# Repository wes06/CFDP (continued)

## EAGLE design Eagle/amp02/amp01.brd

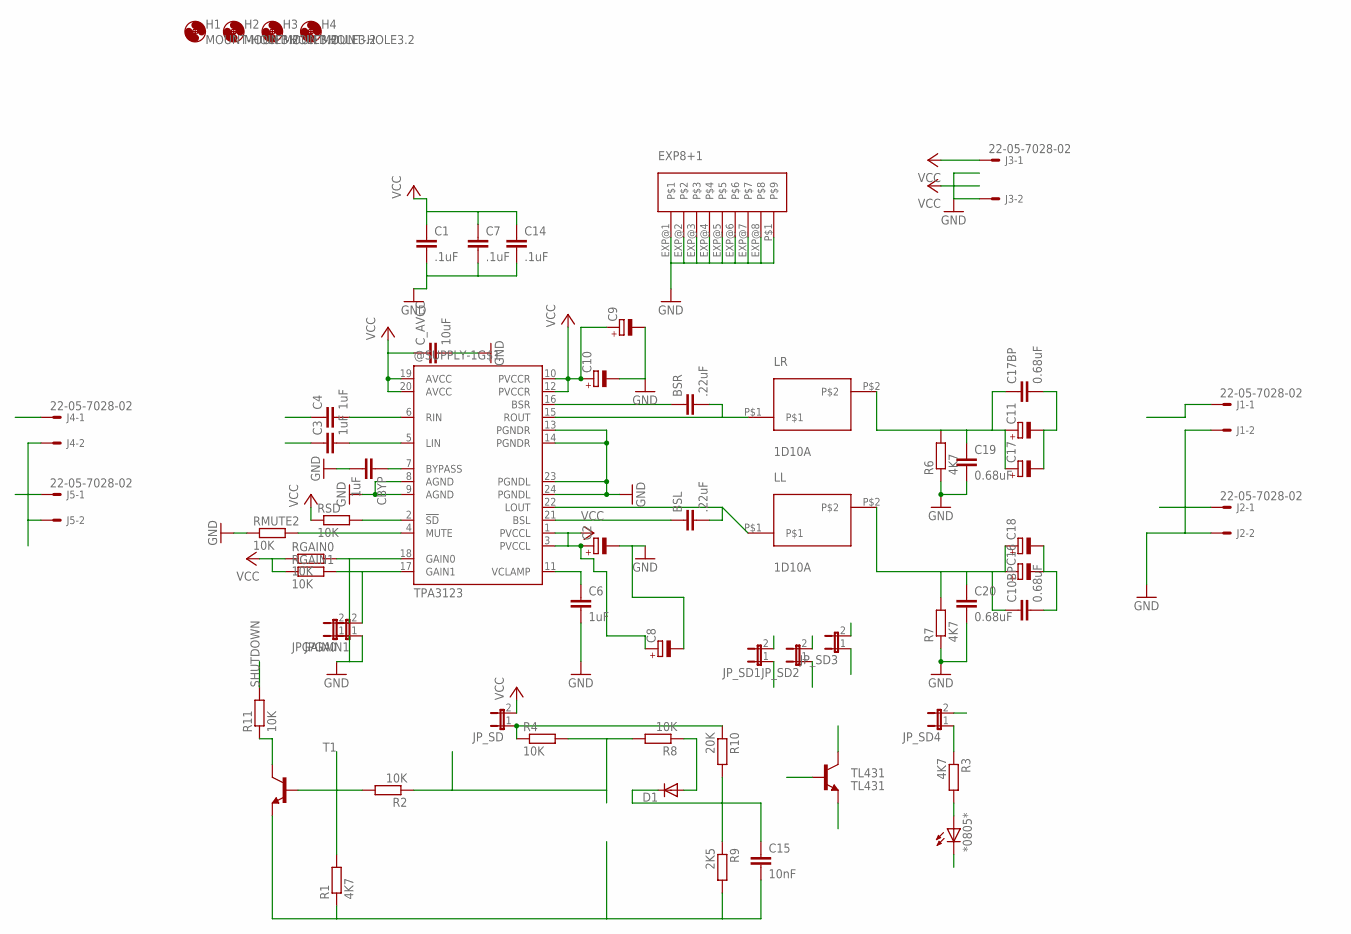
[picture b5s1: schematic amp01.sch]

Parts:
*0805*: LEDCHIP-LED0805; CHIP-LED0805
@SUPPLY-1: TPA3123; PWP-TSSOP24
BSL: .22uF; C0805
BSR: .22uF; C0805
C1, C7, C14: .1uF; C0805
C2, C8, C9, C10, C11, C16, C17, C18: CPOL-EUF; PANASONIC_F
C3, C4: 1uF; C050-050X075
C6: 1uF; C0805
C10BP, C17BP, C19, C20: 0.68uF; C050-055X075
C15: 10nF; C0805
CBYP: 1uF; C0805
C_AVCC: 10uF; C1210
D1: DIODE-MICROMELF-W; MICROMELF-W
H1, H2, H3, H4: MOUNT-HOLE3.2; 3,2
J1, J2, J3, J4, J5: 22-05-7028-02; 7395-02
JPGAIN0, JPGAIN1: JUMPER-2SMD-NC; SJ_2S
JP_SD, JP_SD1, JP_SD2, JP_SD3, JP_SD4: JUMPER-2SMD-NC; SJ_2S
LL: 1D10A; 1D10APAC
LR: 1D10A; 1D10APAC
R1, R3, R6, R7: 4K7; R0805
R2, R4, R8, R11: 10K; R0805
R9: 2K5; R0805
R10: 20K; R0805
RGAIN0, RGAIN1: 10K; R0805
RMUTE2: 10K; R0805
RSD: 10K; R0805
T1: MMBT3904LT1-NPN-SOT23-BEC; SOT23-BEC
TL431: TL431; SOT23

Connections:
GND: *0805*.C, @SUPPLY-1.8 (AGND), @SUPPLY-1.9 (AGND), @SUPPLY-1.13 (PGNDR), @SUPPLY-1.14 (PGNDR), @SUPPLY-1.23 (PGNDL), @SUPPLY-1.24 (PGNDL), @SUPPLY-1.EXP@1, @SUPPLY-1.EXP@2, @SUPPLY-1.EXP@3, @SUPPLY-1.EXP@4, @SUPPLY-1.EXP@5, @SUPPLY-1.EXP@6, @SUPPLY-1.EXP@7, @SUPPLY-1.EXP@8, @SUPPLY-1.P$1, C1.2, C2.-, C6.2, C7.2, C8.-, C9.-, C10.-, C14.2, C15.2, C19.2, C20.2, CBYP.2, C_AVCC.2, J1.2, J2.2, J3.2, J4.2, J5.2, JPGAIN0.1, JPGAIN1.1, JP_SD1.1, JP_SD2.1, JP_SD3.1, R1.1, R6.1, R7.1, R9.2, RMUTE2.1, T1.E, TL431.3 (C)
GND1: JP_SD1.2
GND2: JP_SD2.2, JP_SD3.2
K: R2.1, R4.2, R8.2, TL431.1 (B)
LOUT: C11.-, C17.-, C17BP.2, J1.1
unnamed: @SUPPLY-1.6 (RIN), C4.2
unnamed: @SUPPLY-1.5 (LIN), C3.2
unnamed: C3.1, J5.1
unnamed: JP_SD.1, R4.1, R10.1
unnamed: @SUPPLY-1.11 (VCLAMP), C6.1
unnamed: @SUPPLY-1.4 (MUTE), RMUTE2.2
unnamed: @SUPPLY-1.18 (GAIN0), JPGAIN0.2, RGAIN0.2
unnamed: @SUPPLY-1.17 (GAIN1), JPGAIN1.2, RGAIN1.2
unnamed: C4.1, J4.1
unnamed: @SUPPLY-1.15 (ROUT), BSR.2, LR.P$1
unnamed: @SUPPLY-1.16 (BSR), BSR.1
unnamed: @SUPPLY-1.22 (LOUT), BSL.2, LL.P$1
unnamed: @SUPPLY-1.21 (BSL), BSL.1
unnamed: C10BP.1, C16.+, C18.+, C20.1, LL.P$2, R7.2
unnamed: R1.2, R2.2, T1.B
unnamed: *0805*.A, R3.2
unnamed: C11.+, C17.+, C17BP.1, C19.1, LR.P$2, R6.2
unnamed: JP_SD4.1, R3.1
unnamed: R11.1, T1.C
unnamed: D1.A, R8.1
REF: C15.1, D1.C, R9.1, R10.2, TL431.2 (E)
ROUT: C10BP.2, C16.-, C18.-, J2.1
SHUTDOWN: @SUPPLY-1.2 (!SD), R11.2, RSD.2
VBYP: @SUPPLY-1.7 (BYPASS), CBYP.1
VCC: @SUPPLY-1.1 (PVCCL), @SUPPLY-1.3 (PVCCL), @SUPPLY-1.10 (PVCCR), @SUPPLY-1.12 (PVCCR), @SUPPLY-1.19 (AVCC), @SUPPLY-1.20 (AVCC), C1.1, C2.+, C7.1, C8.+, C9.+, C10.+, C14.1, C_AVCC.1, J3.1, JP_SD.2, JP_SD4.2, RGAIN0.1, RGAIN1.1, RSD.1

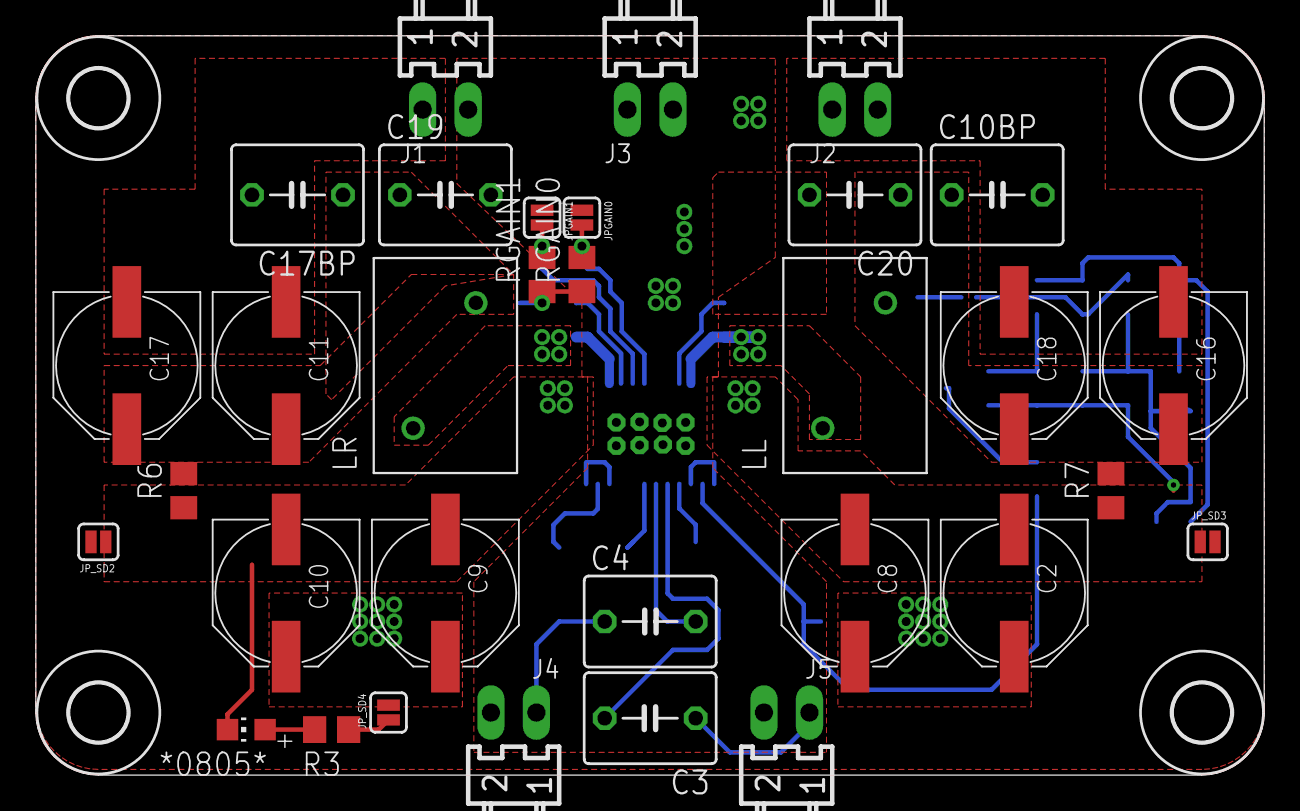
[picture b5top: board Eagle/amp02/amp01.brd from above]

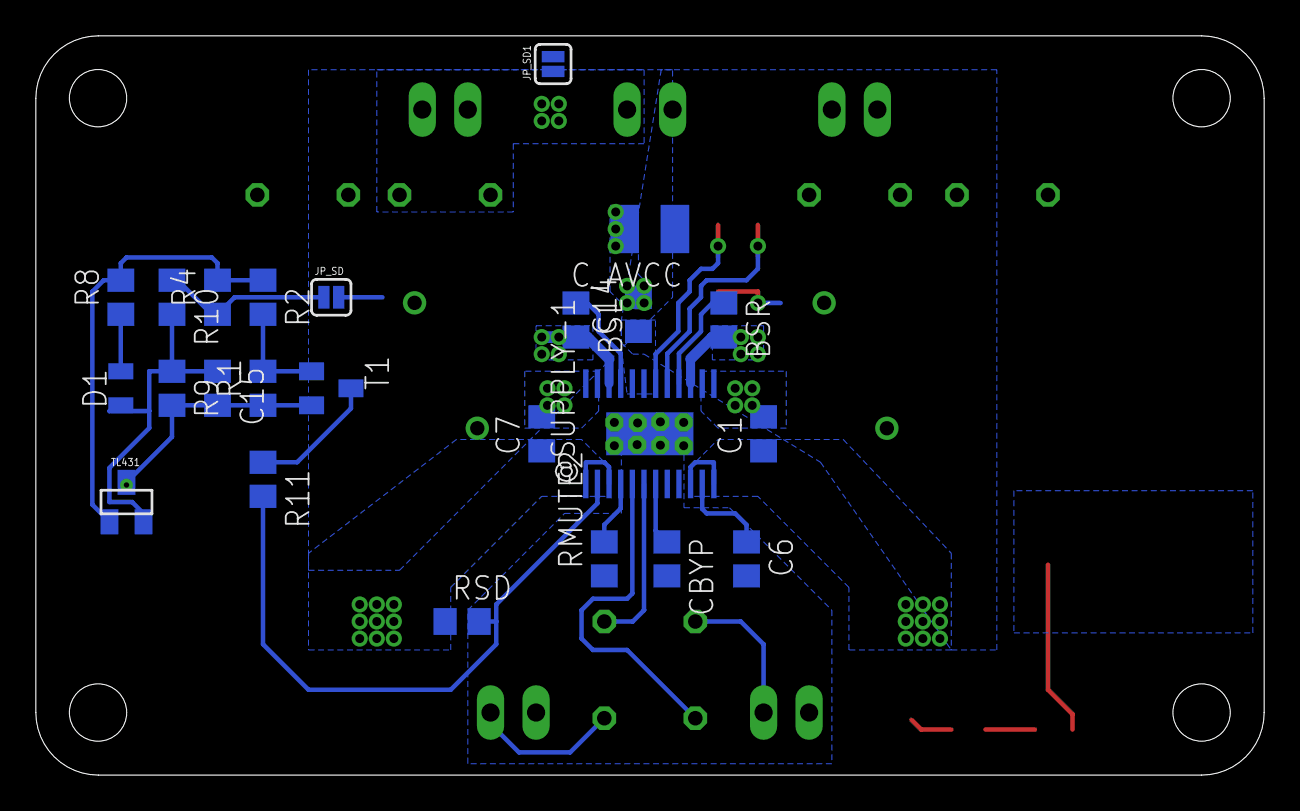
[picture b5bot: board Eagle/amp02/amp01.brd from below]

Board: 2 copper layers, 68.6 x 41.3 mm, 60 parts (24 on the bottom side), 29 nets.

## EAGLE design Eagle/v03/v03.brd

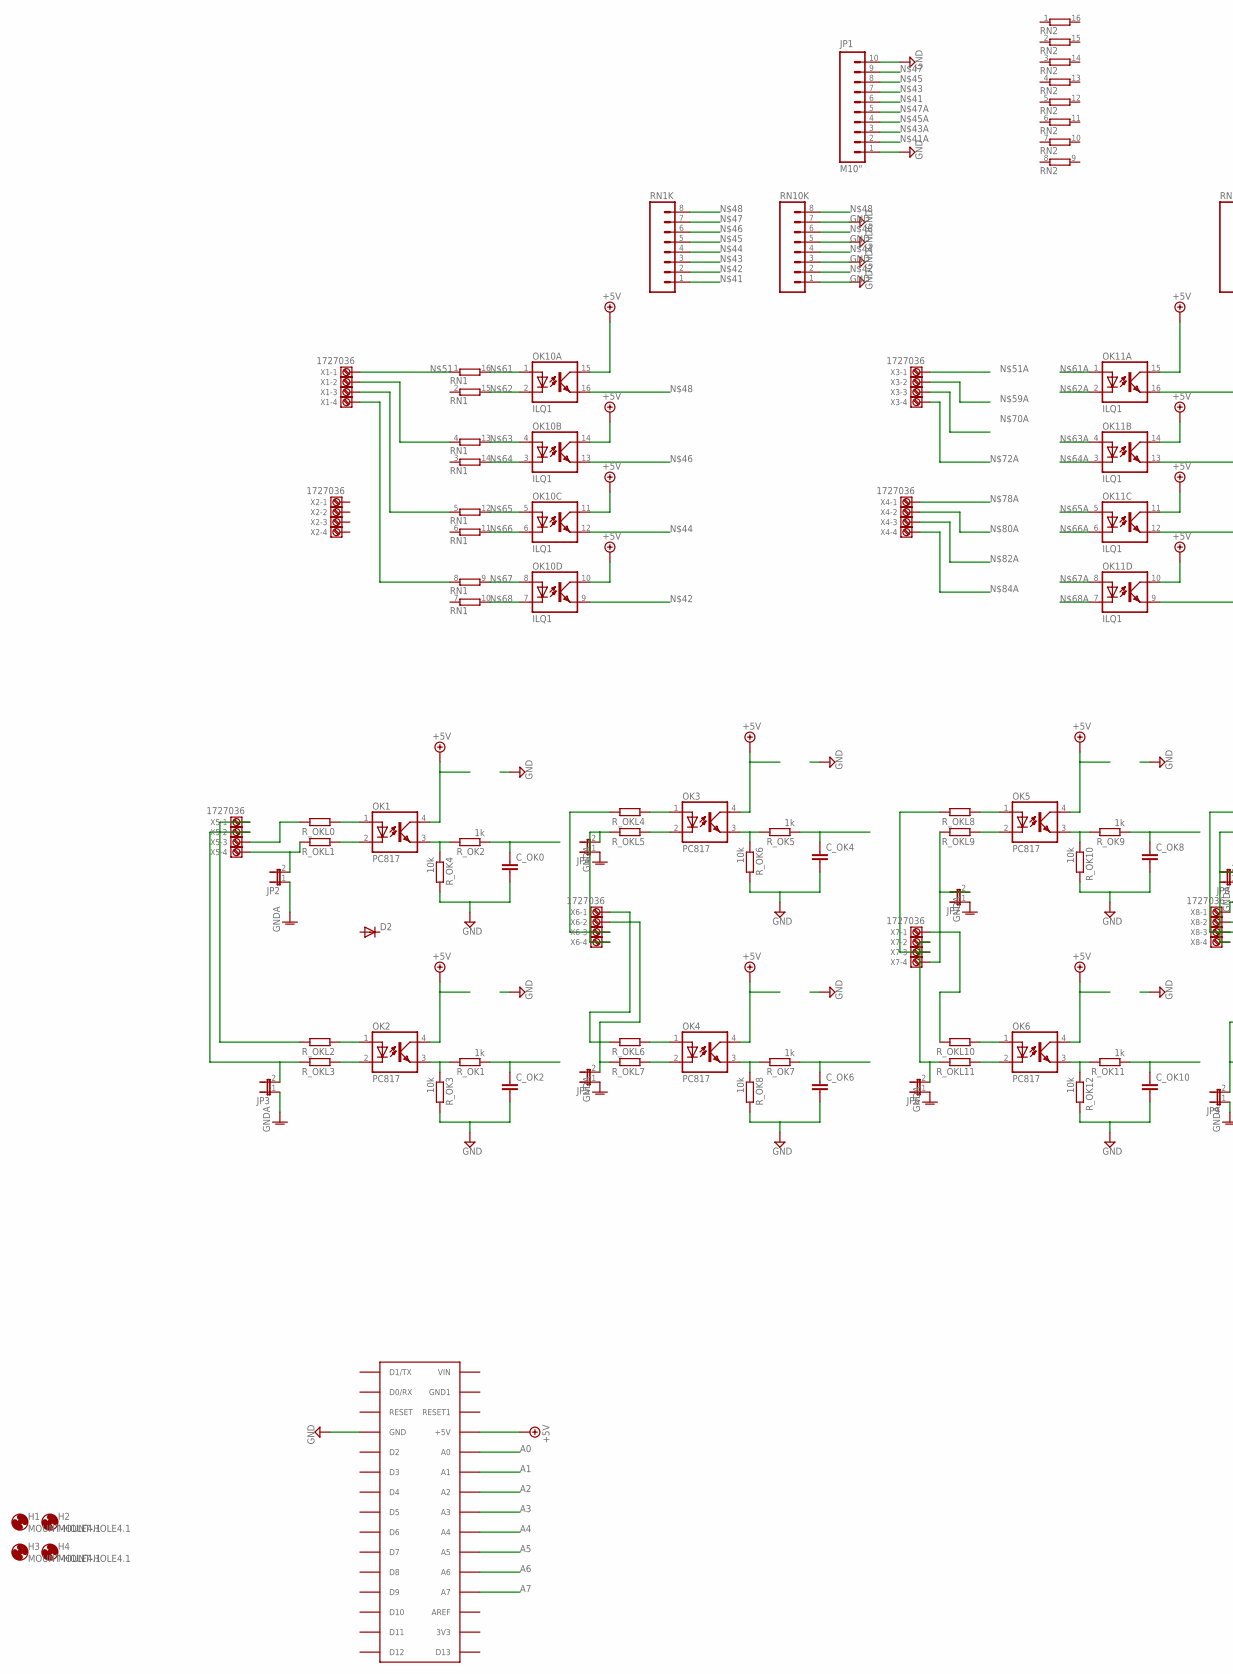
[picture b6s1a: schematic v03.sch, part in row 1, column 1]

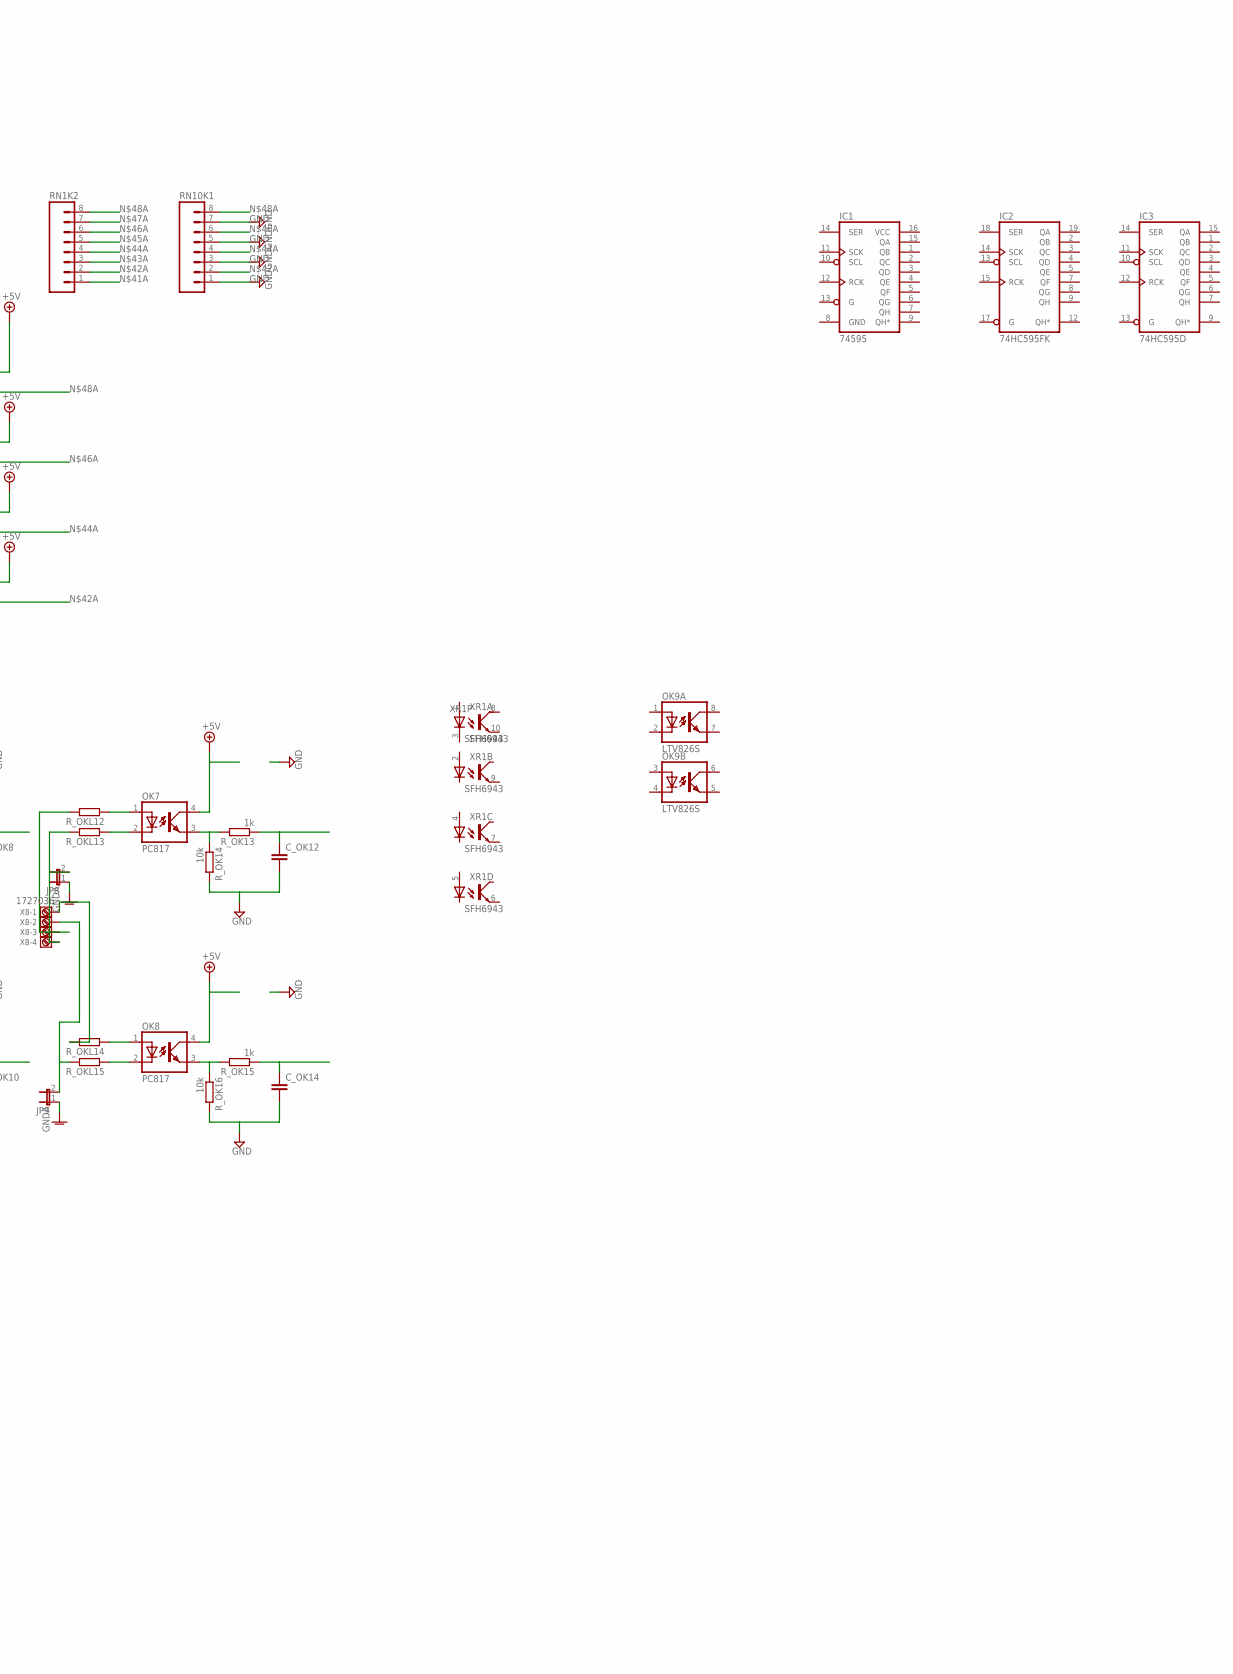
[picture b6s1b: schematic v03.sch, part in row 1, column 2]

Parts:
C_OK0, C_OK2, C_OK4, C_OK6, C_OK8, C_OK10, C_OK12, C_OK14: C-EUC0805; C0805
D2: DIODESOD; SOD-323
H1, H2, H3, H4: MOUNT-HOLE4.1; 4,1
IC1: 74595; TSSOP16
IC2: 74HC595FK; LCC20
IC3: 74HC595D; SO16
JP1: M10"; 1X10
JP2, JP3, JP4, JP5, JP6, JP7, JP8, JP9: JUMPER-2PTH; 1X02
OK1, OK2, OK3, OK4, OK5, OK6, OK7, OK8: PC817; DIL04
OK9: LTV826S; DIL8-SMD
OK10, OK11: ILQ1; DIL16
RN1, RN2: 8R-PSOMC; SOMC16
RN1K, RN1K2, RN10K, RN10K1: M081X08; 1X08
R_OK1, R_OK2, R_OK5, R_OK7, R_OK9, R_OK11, R_OK13, R_OK15: 1k; M0805
R_OK3, R_OK4, R_OK6, R_OK8, R_OK10, R_OK12, R_OK14, R_OK16: 10k; M0805
R_OKL0, R_OKL1, R_OKL2, R_OKL3, R_OKL4, R_OKL5, R_OKL6, R_OKL7, R_OKL8, R_OKL9, R_OKL10, R_OKL11, R_OKL12, R_OKL13, R_OKL14, R_OKL15: R-EU_R1210; R1210
U$1: ARDUINONANO; PDIP-32
X1, X2, X3, X4, X5, X6, X7, X8: 1727036
XR1: SFH6943; SOT223/10

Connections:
+5V: OK1.4 (COL), OK2.4 (COL), OK3.4 (COL), OK4.4 (COL), OK5.4 (COL), OK6.4 (COL), OK7.4 (COL), OK8.4 (COL), OK10.10 (COL), OK10.11 (COL), OK10.14 (COL), OK10.15 (COL), OK11.10 (COL), OK11.11 (COL), OK11.14 (COL), OK11.15 (COL), U$1.+5V
A0: C_OK0.1, R_OK2.1, U$1.A0
A1: C_OK2.1, R_OK1.1, U$1.A1
A2: C_OK4.1, R_OK5.1, U$1.A2
A3: C_OK6.1, R_OK7.1, U$1.A3
A4: C_OK8.1, R_OK9.1, U$1.A4
A5: C_OK10.1, R_OK11.1, U$1.A5
A6: C_OK12.1, R_OK13.1, U$1.A6
A7: C_OK14.1, R_OK15.1, U$1.A7
GND: C_OK0.2, C_OK2.2, C_OK4.2, C_OK6.2, C_OK8.2, C_OK10.2, C_OK12.2, C_OK14.2, IC1.8 (GND), IC2.10 (GND), IC3.8 (GND), JP1.1, JP1.10, RN10K.1, RN10K.3, RN10K.5, RN10K.7, RN10K1.1, RN10K1.3, RN10K1.5, RN10K1.7, R_OK3.2, R_OK4.2, R_OK6.2, R_OK8.2, R_OK10.2, R_OK12.2, R_OK14.2, R_OK16.2, U$1.GND
GNDA: JP2.1, JP3.1, JP4.1, JP5.1, JP6.1, JP7.1, JP8.1, JP9.1
unnamed: OK1.1 (A), R_OKL0.1
unnamed: JP2.2, R_OKL1.2, X5.4
unnamed: OK1.2 (C), R_OKL1.1
unnamed: OK2.1 (A), R_OKL2.1
unnamed: OK1.3 (EMIT), R_OK2.2, R_OK4.1
unnamed: R_OKL14.2, X8.1
unnamed: OK2.3 (EMIT), R_OK1.2, R_OK3.1
unnamed: OK7.1 (A), R_OKL12.1
unnamed: JP3.2, R_OKL3.2, X5.2
unnamed: OK2.2 (C), R_OKL3.1
unnamed: OK3.1 (A), R_OKL4.1
unnamed: R_OKL2.2, X5.1
unnamed: OK3.3 (EMIT), R_OK5.2, R_OK6.1
unnamed: OK7.3 (EMIT), R_OK13.2, R_OK14.1
unnamed: OK3.2 (C), R_OKL5.1
unnamed: OK4.1 (A), R_OKL6.1
unnamed: JP8.2, R_OKL13.2, X8.4
unnamed: OK4.3 (EMIT), R_OK7.2, R_OK8.1
unnamed: OK7.2 (C), R_OKL13.1
unnamed: OK4.2 (C), R_OKL7.1
unnamed: OK5.1 (A), R_OKL8.1
unnamed: JP4.2, R_OKL5.2, X6.4
unnamed: OK5.3 (EMIT), R_OK9.2, R_OK10.1
unnamed: OK8.1 (A), R_OKL14.1
unnamed: OK5.2 (C), R_OKL9.1
unnamed: OK6.1 (A), R_OKL10.1
unnamed: R_OKL6.2, X6.1
unnamed: OK6.3 (EMIT), R_OK11.2, R_OK12.1
unnamed: JP5.2, R_OKL7.2, X6.2
unnamed: OK6.2 (C), R_OKL11.1
unnamed: OK8.3 (EMIT), R_OK15.2, R_OK16.1
unnamed: OK8.2 (C), R_OKL15.1
unnamed: JP1.6, RN1K.1
unnamed: JP1.2, RN1K2.1
unnamed: OK10.9 (EMIT), RN1K.2, RN10K.2
unnamed: OK11.9 (EMIT), RN1K2.2, RN10K1.2
unnamed: JP1.7, RN1K.3
unnamed: JP1.3, RN1K2.3
unnamed: OK10.12 (EMIT), RN1K.4, RN10K.4
unnamed: OK11.12 (EMIT), RN1K2.4, RN10K1.4
unnamed: JP1.8, RN1K.5
unnamed: JP1.4, RN1K2.5
unnamed: OK10.13 (EMIT), RN1K.6, RN10K.6
unnamed: OK11.13 (EMIT), RN1K2.6, RN10K1.6
unnamed: JP1.9, RN1K.7
unnamed: JP1.5, RN1K2.7
unnamed: OK10.16 (EMIT), RN1K.8, RN10K.8
unnamed: OK11.16 (EMIT), RN1K2.8, RN10K1.8
unnamed: R_OKL8.2, X7.3
unnamed: JP7.2, R_OKL9.2, X7.4
unnamed: RN1.1, X1.1
unnamed: JP6.2, R_OKL11.2, X7.2
unnamed: RN1.4 (1), X1.2
unnamed: RN1.5 (1), X1.3
unnamed: JP9.2, R_OKL15.2, X8.2
unnamed: R_OKL10.2, X7.1
unnamed: R_OKL12.2, X8.3
unnamed: R_OKL4.2, X6.3
unnamed: RN1.8 (1), X1.4
unnamed: R_OKL0.2, X5.3
unnamed: OK10.1 (A), RN1.16 (2)
unnamed: OK10.2 (C), RN1.15 (2)
unnamed: OK10.4 (A), RN1.13 (2)
unnamed: OK10.3 (C), RN1.14 (2)
unnamed: OK10.5 (A), RN1.12 (2)
unnamed: OK10.6 (C), RN1.11 (2)
unnamed: OK10.8 (A), RN1.9 (2)
unnamed: OK10.7 (C), RN1.10 (2)
VCC: IC1.16 (VCC), IC2.20 (VCC), IC3.16 (VCC)

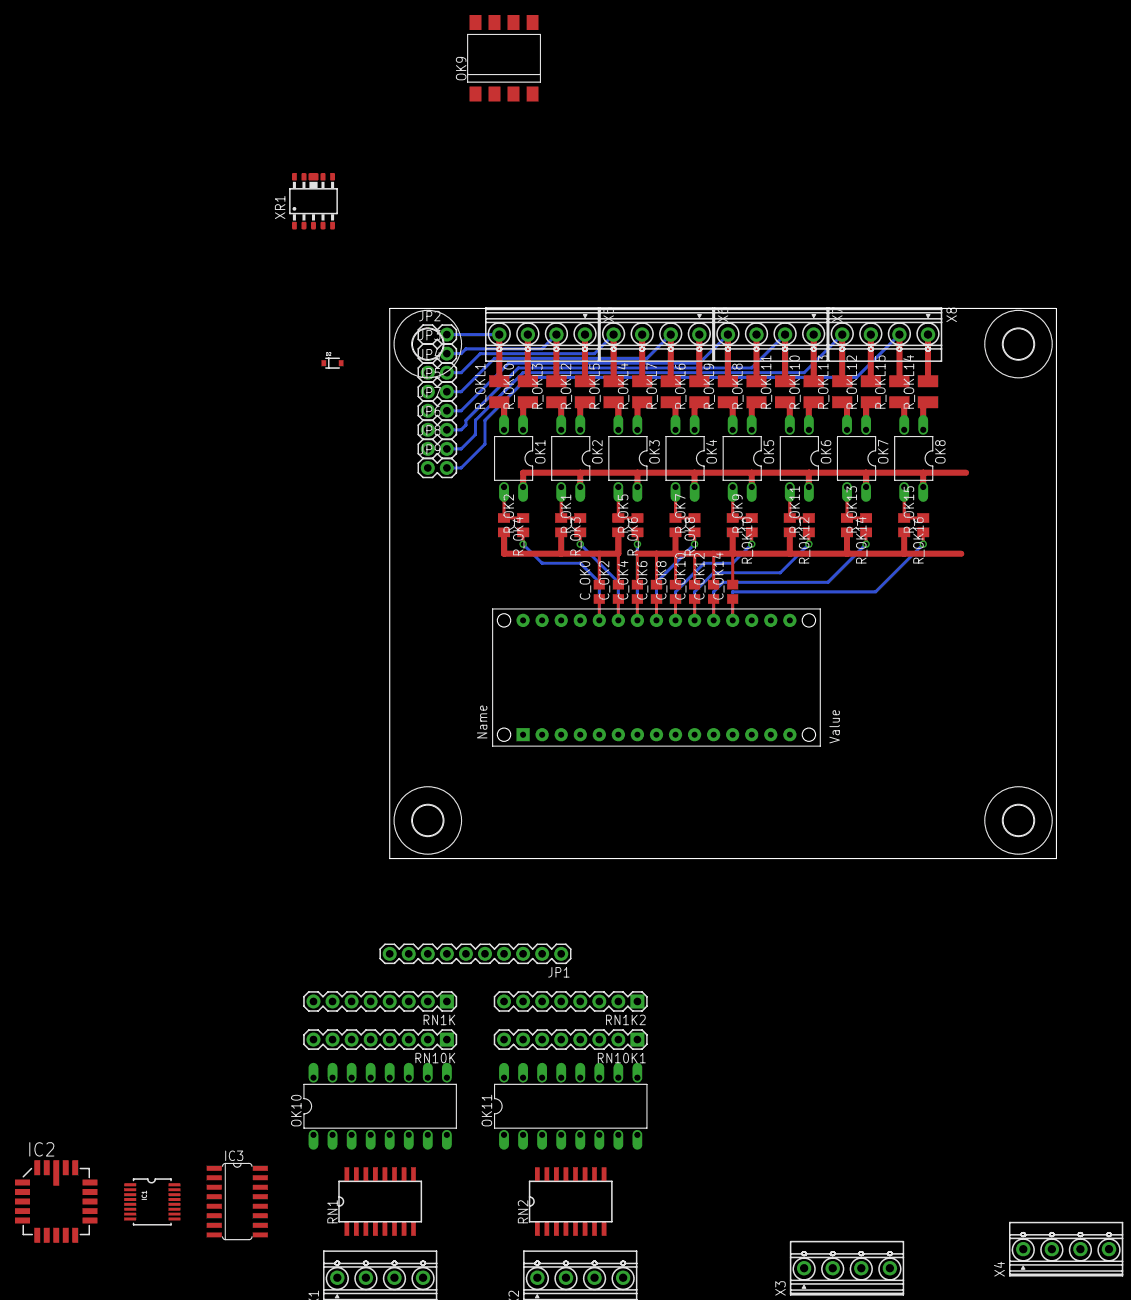
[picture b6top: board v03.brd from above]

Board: 2 copper layers, 88.9 x 73.3 mm, 84 parts (0 on the bottom side), 80 nets.
